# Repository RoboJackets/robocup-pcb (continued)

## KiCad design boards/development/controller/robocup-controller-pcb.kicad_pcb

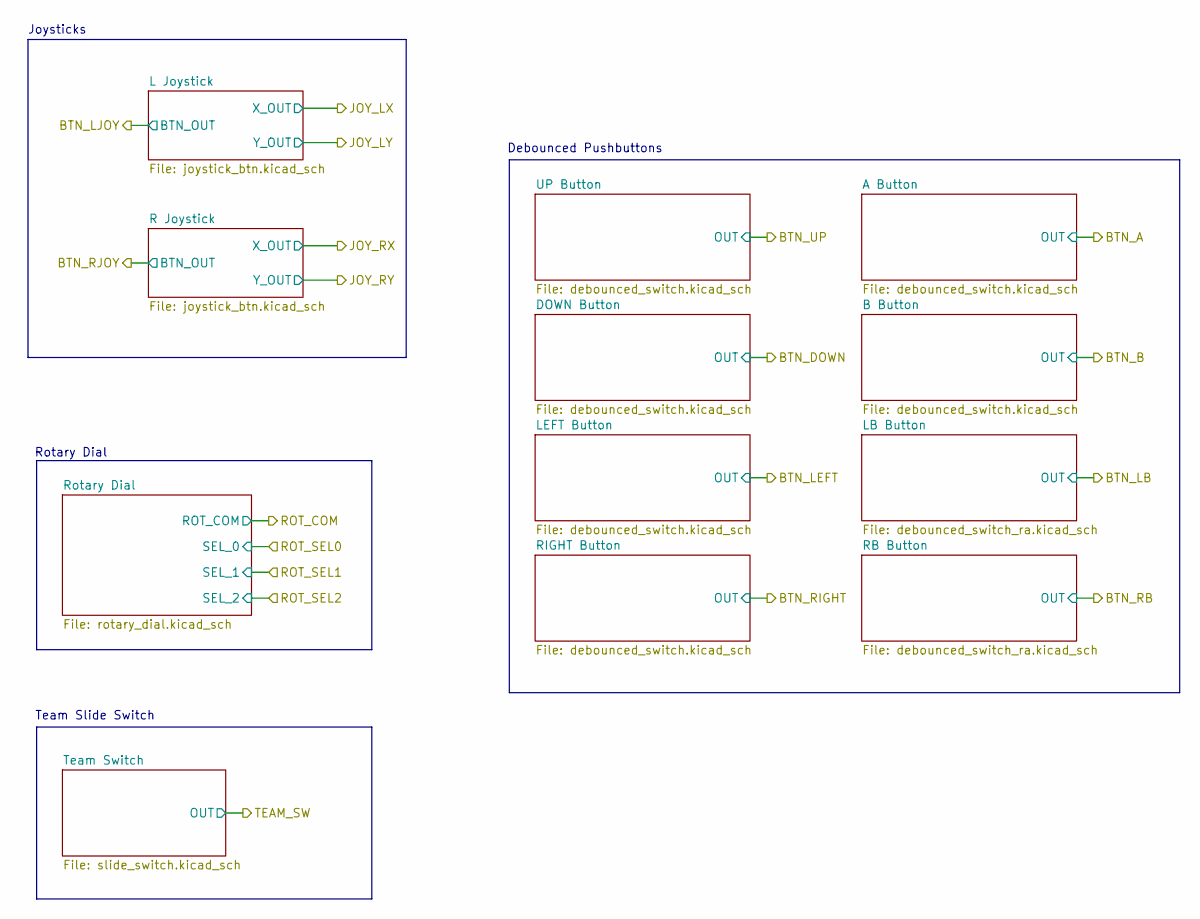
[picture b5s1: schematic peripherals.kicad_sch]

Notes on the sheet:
Debounced Pushbuttons
Joysticks
Team Slide Switch
Rotary Dial

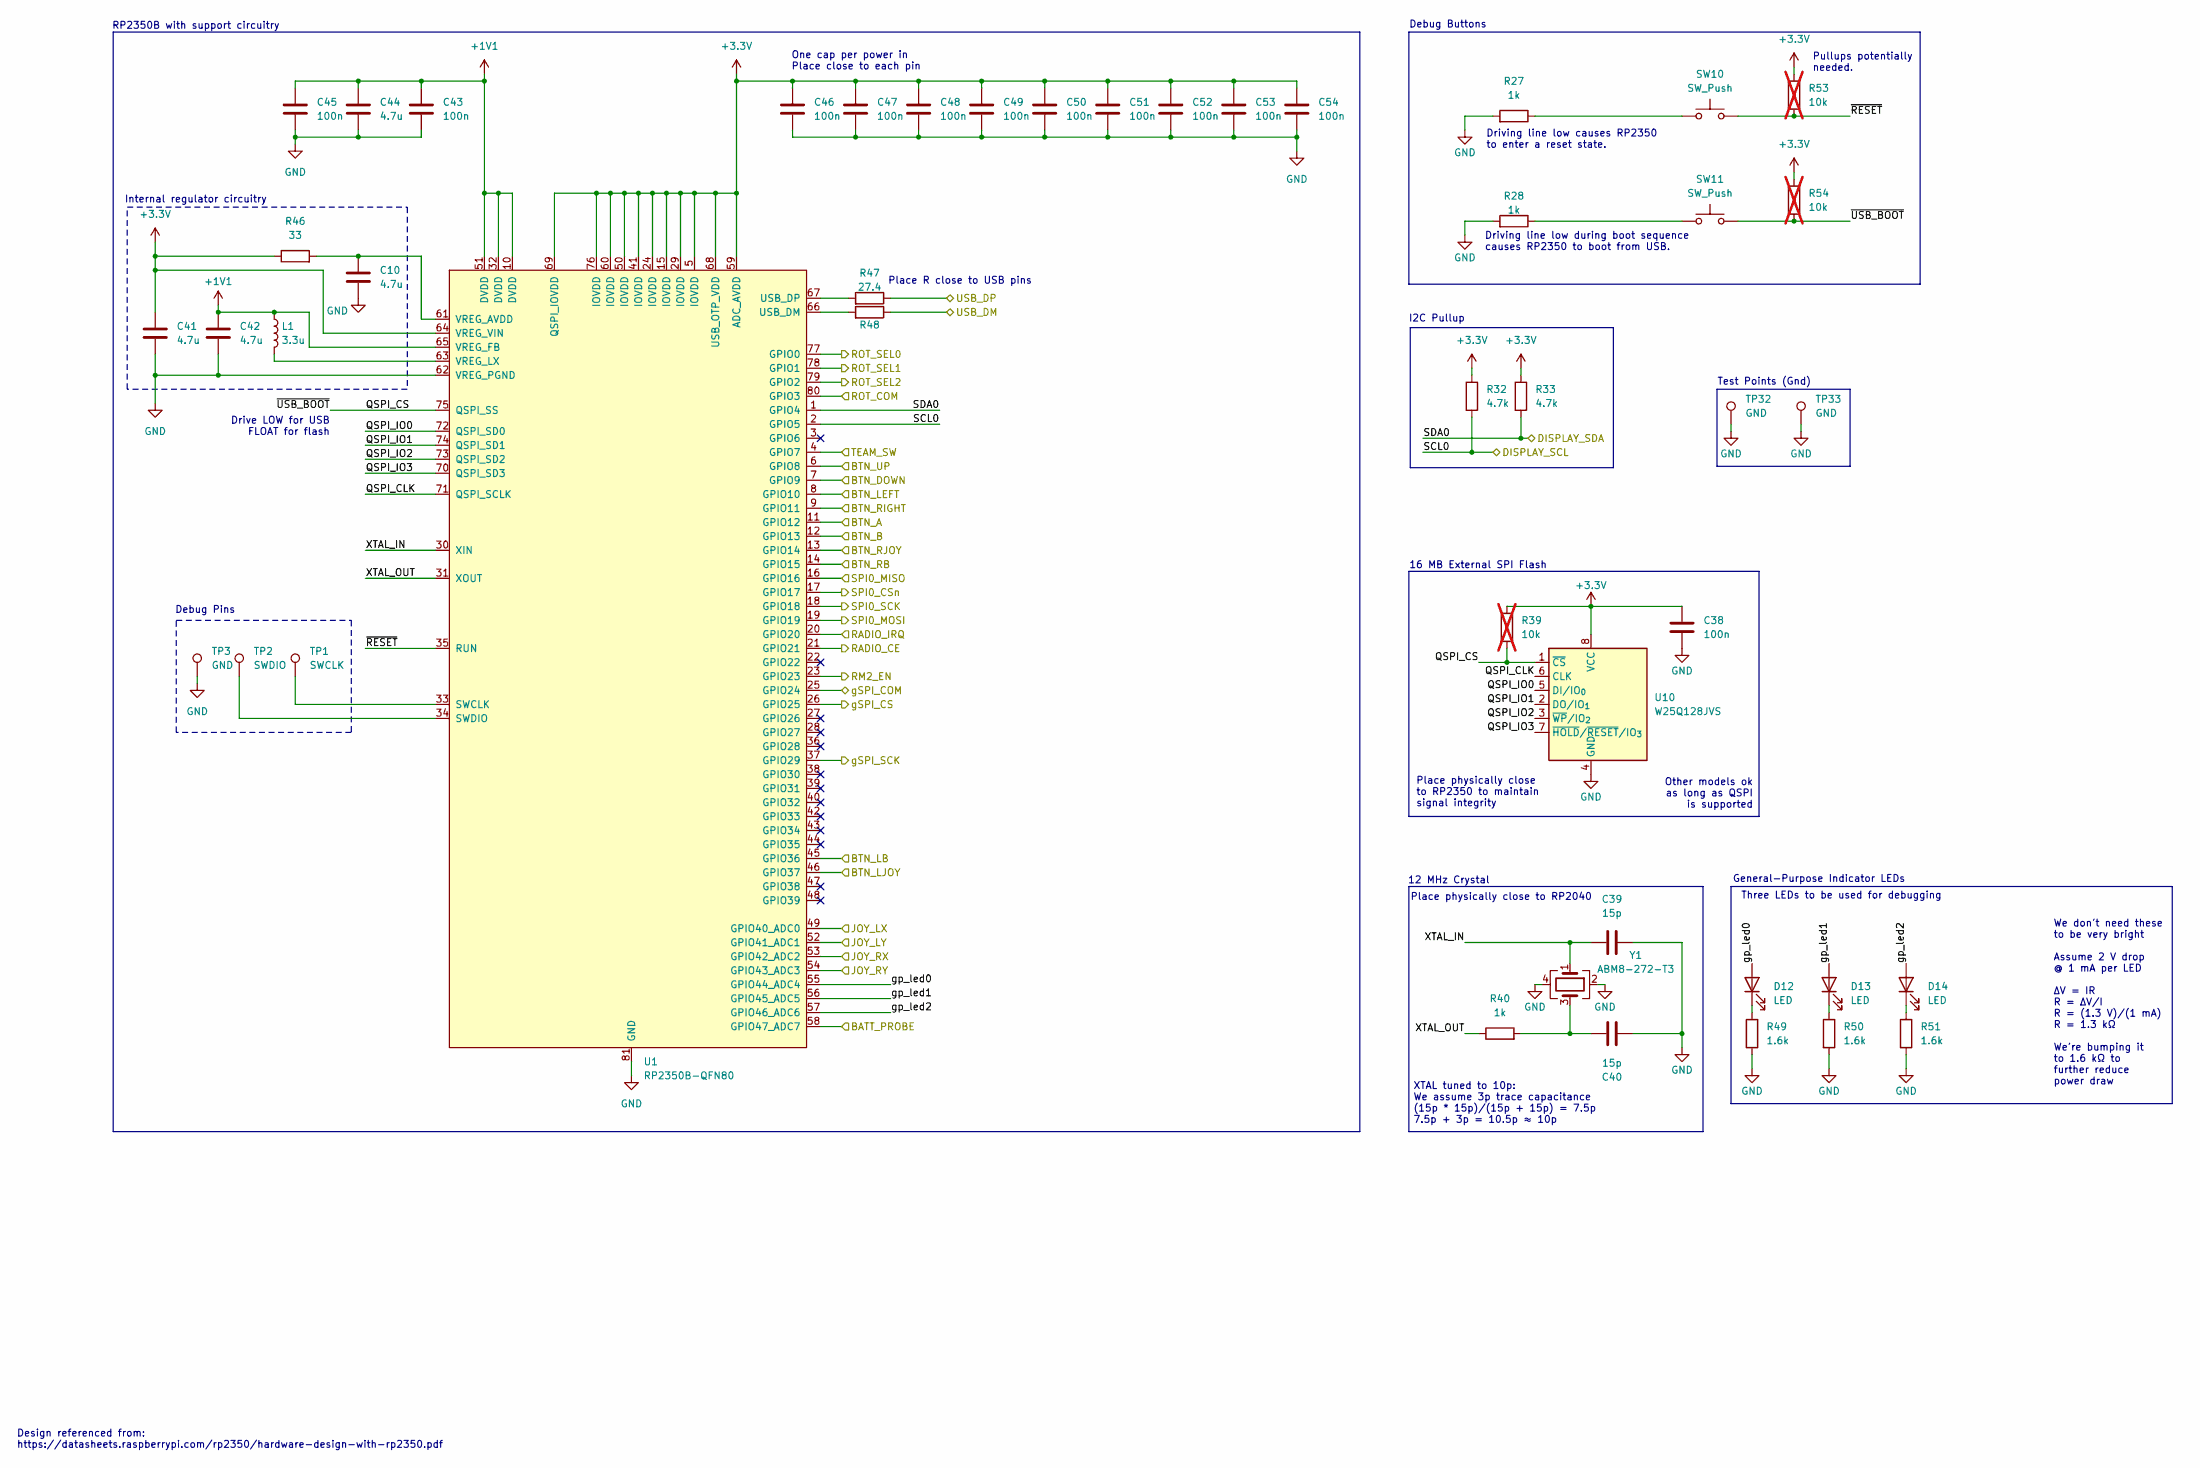
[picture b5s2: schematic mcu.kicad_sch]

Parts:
C10, C41, C42, C44: 4.7u; C_0402_1005Metric
C38, C43, C45, C46, C47, C48, C49, C50, C51, C52, C53, C54: 100n; C_0402_1005Metric
C39, C40: 15p; C_0402_1005Metric
D12, D13, D14: LED; LED_0603_1608Metric
L1: 3.3u; AOTAB201610S3R3101T
R27, R28, R40: 1k; R_0402_1005Metric
R32, R33: 4.7k; R_0402_1005Metric
R39, R53, R54: 10k; R_0402_1005Metric; not fitted
R46: 33; C_0402_1005Metric
R47, R48: 27.4; R_0402_1005Metric
R49, R50, R51: 1.6k; R_0402_1005Metric
SW10, SW11: SW_Push; SW_SKRPABE010
TP1: SWCLK; TestPoint_THTPad_D2.0mm_Drill1.0mm
TP2: SWDIO; TestPoint_THTPad_D2.0mm_Drill1.0mm
TP3: GND; TestPoint_THTPad_2.0x2.0mm_Drill1.0mm
TP32, TP33: GND; TestPoint_Pad_D1.0mm
U1: RP2350B-QFN80; RP2350B_QFN-80_EP_10.573x10.573_Pitch0.4mm
U10: W25Q128JVS; SOIC-8_5.3x5.3mm_P1.27mm; Manufacturer P/N W25Q128JVS
Y1: ABM8-272-T3; Crystal_SMD_Abracon_ABM8AIG-4Pin_3.2x2.5mm; Manufacturer P/N ABM8-272-T3

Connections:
+1V1: C42.1, C43.1, C44.1, C45.1, L1.1, U1.10 (DVDD), U1.32 (DVDD), U1.51 (DVDD), U1.65 (VREG_FB)
+3.3V: C38.1, C41.1, C46.1, C47.1, C48.1, C49.1, C50.1, C51.1, C52.1, C53.1, C54.1, R32.1, R33.1, R39.1, R46.1, R53.1, R54.1, U1.5 (IOVDD), U1.15 (IOVDD), U1.24 (IOVDD), U1.29 (IOVDD), U1.41 (IOVDD), U1.50 (IOVDD), U1.59 (ADC_AVDD), U1.60 (IOVDD), U1.64 (VREG_VIN), U1.68 (USB_OTP_VDD), U1.69 (QSPI_IOVDD), U1.76 (IOVDD), U10.8 (VCC); also elsewhere on the board
/Comms/CE: U1.21 (GPIO21); also elsewhere on the board
/Comms/IRQ: U1.20 (GPIO20); also elsewhere on the board
/Comms/MISO: U1.16 (GPIO16); also elsewhere on the board
/Comms/MOSI: U1.19 (GPIO19); also elsewhere on the board
/Comms/RM2_EN: U1.23 (GPIO23); also elsewhere on the board
/Comms/SCK: U1.18 (GPIO18); also elsewhere on the board
/Comms/gSPI_CS: U1.26 (GPIO25); also elsewhere on the board
/Comms/gSPI_DI: U1.25 (GPIO24); also elsewhere on the board
/Comms/gSPI_SCK: U1.37 (GPIO29); also elsewhere on the board
/Comms/~CS: U1.17 (GPIO17); also elsewhere on the board
/MCU/BATT_PROBE: U1.58 (GPIO47_ADC7); also elsewhere on the board
/MCU/BTN_A: U1.11 (GPIO12); also elsewhere on the board
/MCU/BTN_B: U1.12 (GPIO13); also elsewhere on the board
/MCU/BTN_DOWN: U1.7 (GPIO9); also elsewhere on the board
/MCU/BTN_LB: U1.45 (GPIO36); also elsewhere on the board
/MCU/BTN_LEFT: U1.8 (GPIO10); also elsewhere on the board
/MCU/BTN_LJOY: U1.46 (GPIO37); also elsewhere on the board
/MCU/BTN_RB: U1.14 (GPIO15); also elsewhere on the board
/MCU/BTN_RIGHT: U1.9 (GPIO11); also elsewhere on the board
/MCU/BTN_RJOY: U1.13 (GPIO14); also elsewhere on the board
/MCU/BTN_UP: U1.6 (GPIO8); also elsewhere on the board
/MCU/JOY_LX: U1.49 (GPIO40_ADC0); also elsewhere on the board
/MCU/JOY_LY: U1.52 (GPIO41_ADC1); also elsewhere on the board
/MCU/JOY_RX: U1.53 (GPIO42_ADC2); also elsewhere on the board
/MCU/JOY_RY: U1.54 (GPIO43_ADC3); also elsewhere on the board
/MCU/QSPI_CLK: U1.71 (QSPI_SCLK), U10.6 (CLK)
/MCU/QSPI_CS: R39.2, R54.2, SW11.2, U1.75 (QSPI_SS), U10.1 (~CS)
/MCU/QSPI_IO0: U1.72 (QSPI_SD0), U10.5 (DI/IO_{0})
/MCU/QSPI_IO1: U1.74 (QSPI_SD1), U10.2 (DO/IO_{1})
/MCU/QSPI_IO2: U1.73 (QSPI_SD2), U10.3 (~WP/IO_{2})
/MCU/QSPI_IO3: U1.70 (QSPI_SD3), U10.7 (~HOLD/~RESET/IO_{3})
/MCU/ROT_COM: U1.80 (GPIO3); also elsewhere on the board
/MCU/ROT_SEL0: U1.77 (GPIO0); also elsewhere on the board
/MCU/ROT_SEL1: U1.78 (GPIO1); also elsewhere on the board
/MCU/ROT_SEL2: U1.79 (GPIO2); also elsewhere on the board
/MCU/SCL0: R32.2, U1.2 (GPIO5); also elsewhere on the board
/MCU/SDA0: R33.2, U1.1 (GPIO4); also elsewhere on the board
/MCU/TEAM_SW: U1.4 (GPIO7); also elsewhere on the board
/MCU/USB_DM: R48.1; also elsewhere on the board
/MCU/USB_DP: R47.1; also elsewhere on the board
/MCU/XTAL_IN: C39.2, U1.30 (XIN), Y1.1
/MCU/XTAL_OUT: R40.1, U1.31 (XOUT)
/MCU/gp_led0: D12.2 (A), U1.55 (GPIO44_ADC4)
/MCU/gp_led1: D13.2 (A), U1.56 (GPIO45_ADC5)
/MCU/gp_led2: D14.2 (A), U1.57 (GPIO46_ADC6)
/MCU/~RESET: R53.2, SW10.2, U1.35 (RUN)
GND: C10.2, C38.2, C39.1, C40.2, C41.2, C42.2, C43.2, C44.2, C45.2, C46.2, C47.2, C48.2, C49.2, C50.2, C51.2, C52.2, C53.2, C54.2, R27.2, R28.2, R49.2, R50.2, R51.2, TP3.1 (1_1), TP32.1 (1_1), TP33.1 (1_1), U1.62 (VREG_PGND), U1.81 (GND), U10.4 (GND), Y1.2, Y1.4; also elsewhere on the board
unnamed: C40.1, R40.2, Y1.3
unnamed: D12.1 (K), R49.1
unnamed: D13.1 (K), R50.1
unnamed: D14.1 (K), R51.1
unnamed: R27.1, SW10.1
unnamed: R28.1, SW11.1
unnamed: TP1.1 (1_1), U1.33 (SWCLK)
unnamed: TP2.1 (1_1), U1.34 (SWDIO)
unnamed: R48.2, U1.66 (USB_DM)
unnamed: R47.2, U1.67 (USB_DP)
unnamed: C10.1, R46.2, U1.61 (VREG_AVDD)
unnamed: L1.2, U1.63 (VREG_LX)

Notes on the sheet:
Three LEDs to be used for debugging
XTAL tuned to 10p: We assume 3p trace capacitance (15p * 15p)/(15p + 15p) = 7.5p 7.5p + 3p = 10.5p ≈ 10p
Debug Buttons
Place physically close to RP2350 to maintain signal integrity
Driving line low causes RP2350 to enter a reset state.
Place physically close to RP2040
Design referenced from: https://datasheets.raspberrypi.com/rp2350/hardware-design-with-rp2350.pdf
RP2350B with support circuitry
We don't need these to be very bright Assume 2 V drop @ 1 mA per LED ΔV = IR R = ΔV/I R = (1.3 V)/(1 mA) R = 1.3 kΩ We're bumping it to 1.6 kΩ to further reduce power draw
General-Purpose Indicator LEDs
Pullups potentially needed.
12 MHz Crystal
Driving line low during boot sequence causes RP2350 to boot from USB.
Internal regulator circuitry
Place R close to USB pins
One cap per power in Place close to each pin
16 MB External SPI Flash
Other models ok as long as QSPI is supported
Drive LOW for USB FLOAT for flash
Debug Pins
Test Points (Gnd)
I2C Pullup

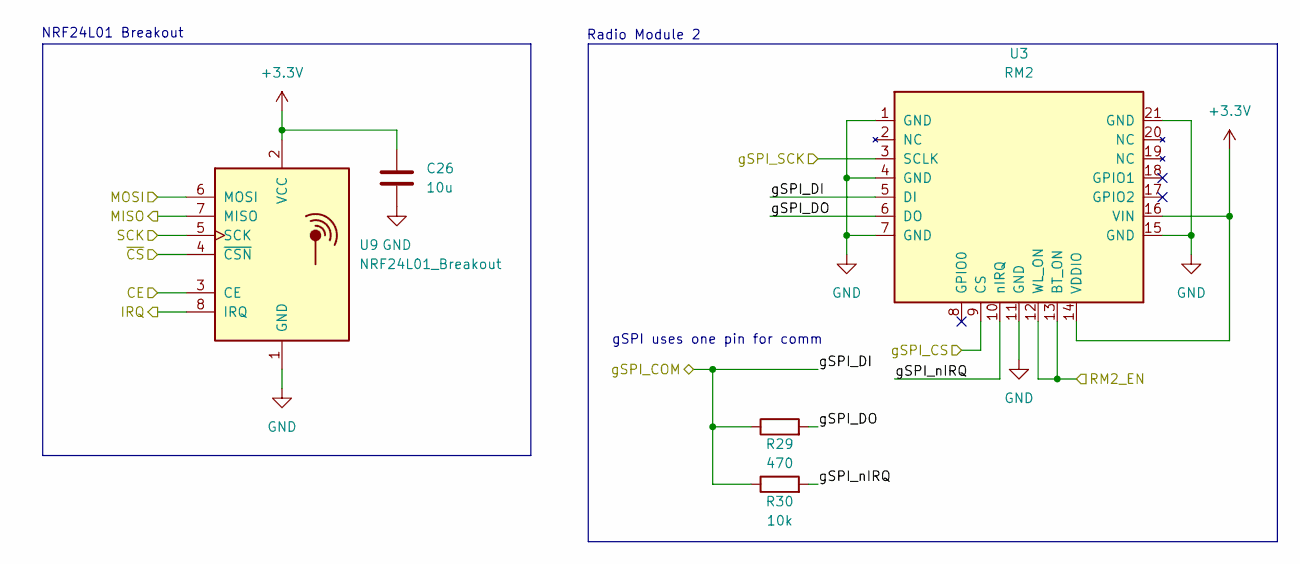
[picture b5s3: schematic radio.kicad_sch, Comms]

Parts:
C26: 10u; C_0603_1608Metric
R29: 470; R_0402_1005Metric
R30: 10k; R_0402_1005Metric
U3: RM2; rpi_rmc20452t
U9: NRF24L01_Breakout; nRF24L01_Breakout

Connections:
+3.3V: C26.2, U3.14 (VDDIO), U3.16 (VIN), U9.2 (VCC); also elsewhere on the board
/Comms/CE: U9.3 (CE); also elsewhere on the board
/Comms/IRQ: U9.8 (IRQ); also elsewhere on the board
/Comms/MISO: U9.7 (MISO); also elsewhere on the board
/Comms/MOSI: U9.6 (MOSI); also elsewhere on the board
/Comms/RM2_EN: U3.12 (WL_ON), U3.13 (BT_ON); also elsewhere on the board
/Comms/SCK: U9.5 (SCK); also elsewhere on the board
/Comms/gSPI_CS: U3.9 (CS); also elsewhere on the board
/Comms/gSPI_DI: R29.1, R30.1, U3.5 (DI); also elsewhere on the board
/Comms/gSPI_DO: R29.2, U3.6 (DO)
/Comms/gSPI_SCK: U3.3 (SCLK); also elsewhere on the board
/Comms/gSPI_nIRQ: R30.2, U3.10 (nIRQ)
/Comms/~CS: U9.4 (~CSN); also elsewhere on the board
GND: C26.1, U3.1 (GND), U3.4 (GND), U3.7 (GND), U3.11 (GND), U3.15 (GND), U3.21 (GND), U9.1 (GND); also elsewhere on the board

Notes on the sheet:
NRF24L01 Breakout
gSPI uses one pin for comm
Radio Module 2

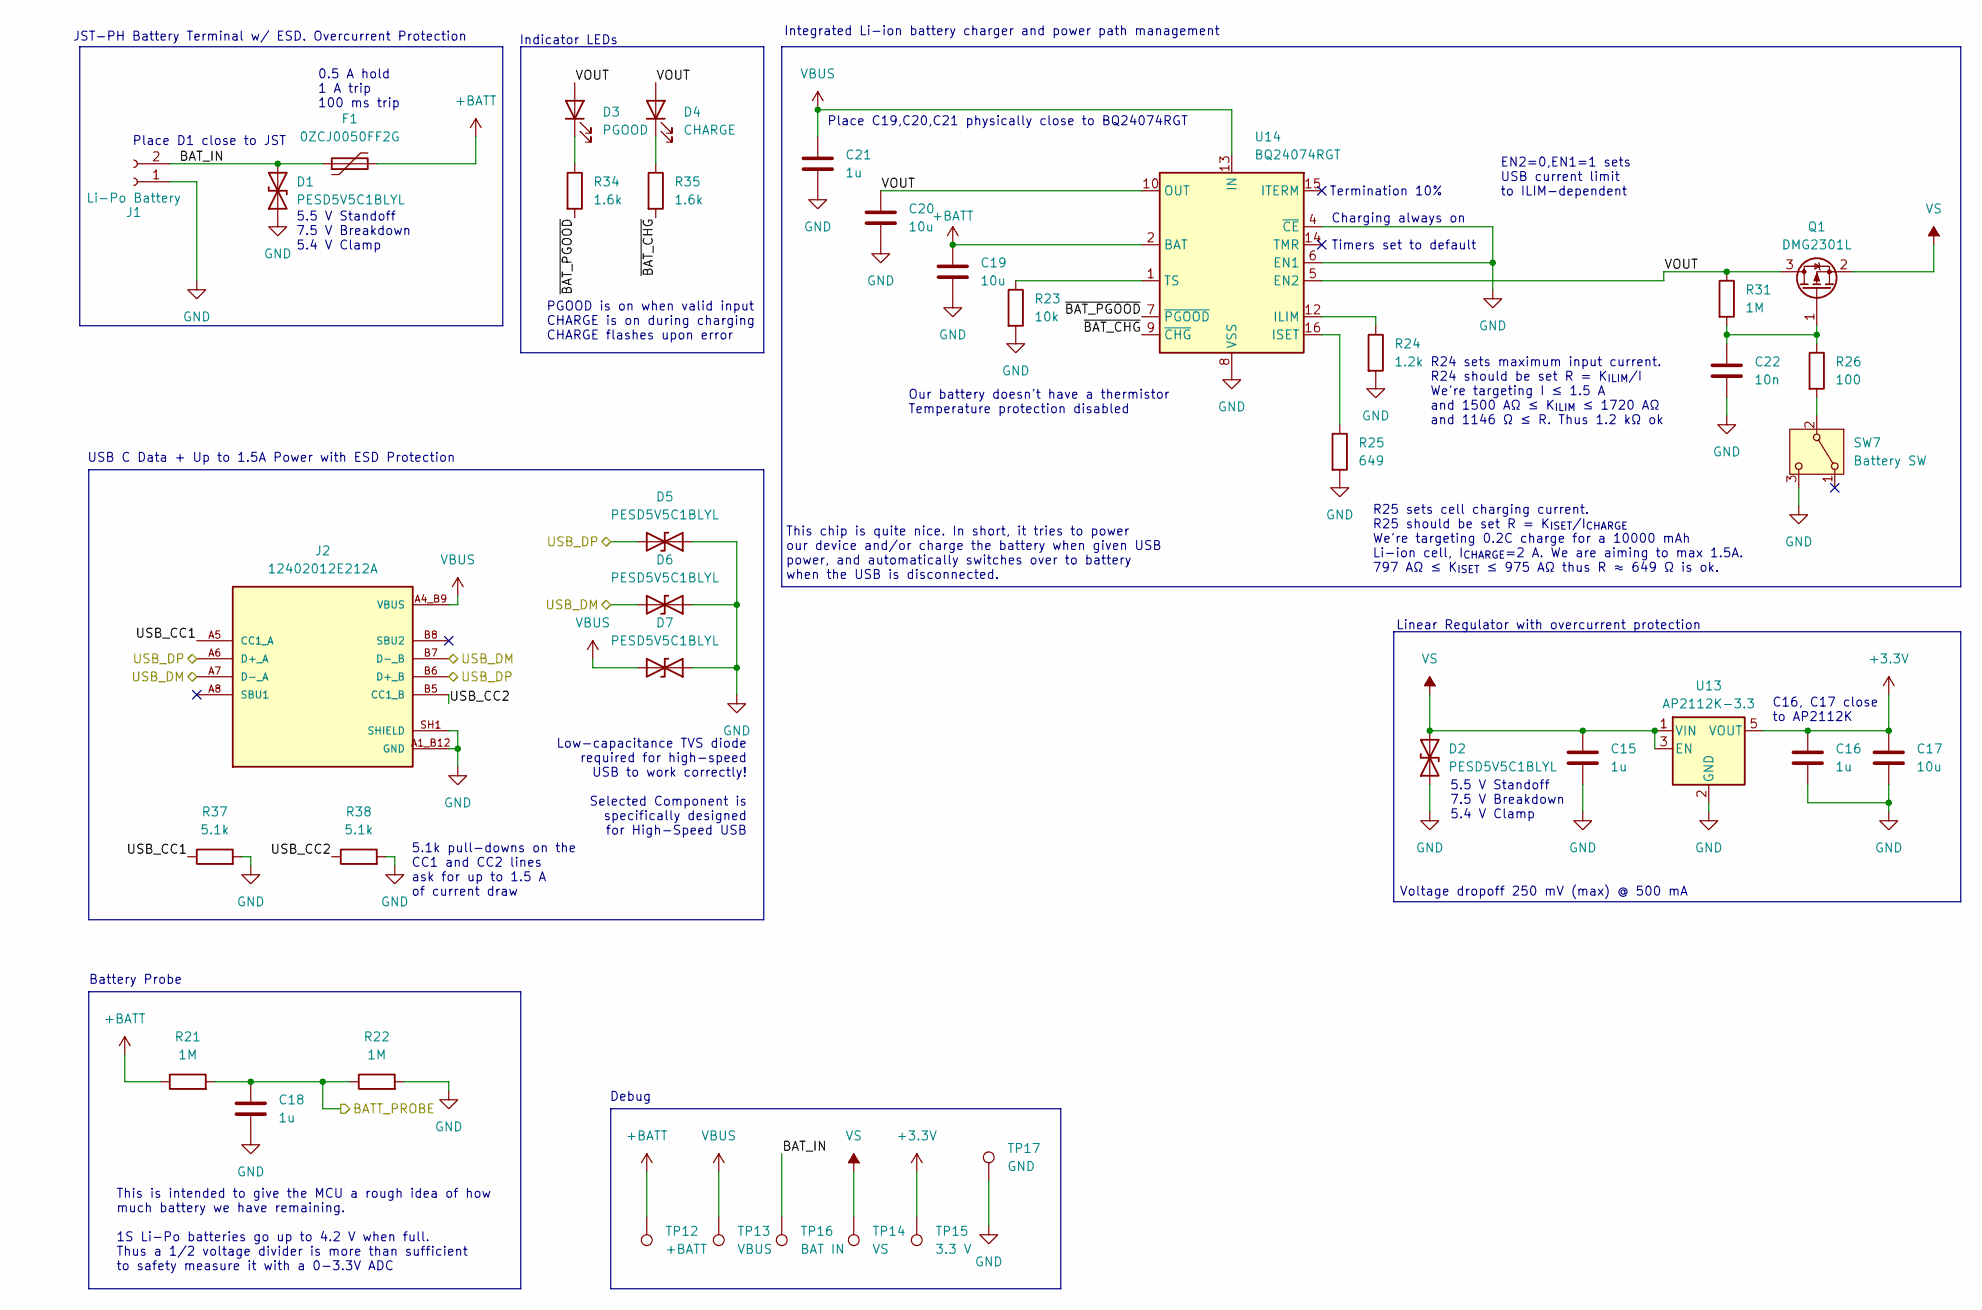
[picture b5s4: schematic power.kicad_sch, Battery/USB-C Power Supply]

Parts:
C15, C16, C18, C21: 1u; C_0402_1005Metric
C17, C19, C20: 10u; C_0402_1005Metric
C22: 10n; C_0402_1005Metric
D1, D2, D5, D6, D7: PESD5V5C1BLYL; D_SOD-882D
D3: PGOOD; LED_0603_1608Metric
D4: CHARGE; LED_0603_1608Metric
F1: 0ZCJ0050FF2G; Fuse_1206_3216Metric
J1: Li-Po Battery; JST_PH_S2B-PH-K_1x02_P2.00mm_Horizontal
J2: 12402012E212A; AMPHENOL_12402012E212A; PARTREV 4
Q1: DMG2301L; SOT-23
R21, R22, R31: 1M; R_0402_1005Metric
R23: 10k; R_0402_1005Metric
R24: 1.2k; R_0402_1005Metric
R25: 649; R_0402_1005Metric
R26: 100; R_0402_1005Metric
R34, R35: 1.6k; R_0402_1005Metric
R37, R38: 5.1k; R_0402_1005Metric
SW7: Battery SW; OS102011MA1QN1_CNK
TP12: +BATT; TestPoint_Pad_D1.0mm
TP13: VBUS; TestPoint_Pad_D1.0mm
TP14: VS; TestPoint_Pad_D1.0mm
TP15: 3.3 V; TestPoint_Pad_D1.0mm
TP16: BAT IN; TestPoint_Pad_D1.0mm
TP17: GND; TestPoint_Pad_D1.0mm
U13: AP2112K-3.3; SOT-23-5
U14: BQ24074RGT; VQFN-16-1EP_3x3mm_P0.5mm_EP1.6x1.6mm

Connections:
+3.3V: C16.1, C17.1, TP15.1 (1_1), U13.5 (VOUT); also elsewhere on the board
+BATT: C19.1, F1.2, R21.1, TP12.1 (1_1), U14.2 (BAT), U14.3 (BAT)
/MCU/BATT_PROBE: C18.1, R21.2, R22.1; also elsewhere on the board
/MCU/USB_DM: D6.2 (A2), J2.A7 (D-_A), J2.B7 (D-_B); also elsewhere on the board
/MCU/USB_DP: D5.2 (A2), J2.A6 (D+_A), J2.B6 (D+_B); also elsewhere on the board
/Power/BAT_IN: D1.2 (A2), F1.1, J1.2, TP16.1 (1_1)
/Power/USB_CC1: J2.A5 (CC1_A), R37.1
/Power/USB_CC2: J2.B5 (CC1_B), R38.1
/Power/VOUT: C20.1, D3.2 (A), D4.2 (A), Q1.3 (D), R31.1, U14.5 (EN2), U14.10 (OUT), U14.11 (OUT)
/Power/~BAT_CHG: R35.2, U14.9 (~CHG)
/Power/~BAT_PGOOD: R34.2, U14.7 (~PGOOD)
GND: C15.2, C16.2, C17.2, C18.2, C19.2, C20.2, C21.2, C22.2, D1.1 (A1), D2.1 (A1), D5.1 (A1), D6.1 (A1), D7.1 (A1), J1.1, J2.A1_B12 (GND), J2.B1_A12 (GND), J2.SH1 (SHIELD), J2.SH2 (SHIELD), J2.SH3 (SHIELD), J2.SH4 (SHIELD), R22.2, R23.2, R24.2, R25.2, R37.2, R38.2, SW7.3 (C), TP17.1 (1_1), U13.2 (GND), U14.4 (~CE), U14.6 (EN1), U14.8 (VSS), U14.17 (VSS); also elsewhere on the board
unnamed: D3.1 (K), R34.1
unnamed: D4.1 (K), R35.1
unnamed: C22.1, Q1.1 (G), R26.1, R31.2
unnamed: R26.2, SW7.2 (B)
unnamed: R24.1, U14.12 (ILIM)
unnamed: R25.1, U14.16 (ISET)
unnamed: R23.1, U14.1 (TS)
VBUS: C21.1, D7.2 (A2), J2.A4_B9 (VBUS), J2.B4_A9 (VBUS), TP13.1 (1_1), U14.13 (IN)
VS: C15.1, D2.2 (A2), Q1.2 (S), TP14.1 (1_1), U13.1 (VIN), U13.3 (EN)

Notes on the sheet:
Termination 10%
R25 sets cell charging current. R25 should be set R = K_{ISET}/I_{CHARGE} We're targeting 0.2C charge for a 10000 mAh Li-ion cell, I_{CHARGE}=2 A. We are aiming to max 1.5A. 797 AΩ ≤ K_{ISET} ≤ 975 AΩ thus R ≈ 649 Ω is ok.
Indicator LEDs
This chip is quite nice. In short, it tries to power our device and/or charge the battery when given USB power, and automatically switches over to battery when the USB is disconnected.
R24 sets maximum input current. R24 should be set R = K_{ILIM}/I We're targeting I ≤ 1.5 A and 1500 AΩ ≤ K_{ILIM} ≤ 1720 AΩ and 1146 Ω ≤ R. Thus 1.2 kΩ ok
Battery Probe
EN2=0,EN1=1 sets USB current limit to ILIM-dependent
0.5 A hold 1 A trip 100 ms trip
This is intended to give the MCU a rough idea of how much battery we have remaining. 1S Li-Po batteries go up to 4.2 V when full. Thus a 1/2 voltage divider is more than sufficient to safety measure it with a 0-3.3V ADC
Debug
5.1k pull-downs on the CC1 and CC2 lines ask for up to 1.5 A of current draw
Place D1 close to JST
5.5 V Standoff 7.5 V Breakdown 5.4 V Clamp
Charging always on
Voltage dropoff 250 mV (max) @ 500 mA
Integrated Li-ion battery charger and power path management
Timers set to default
Our battery doesn't have a thermistor Temperature protection disabled
C16, C17 close to AP2112K
PGOOD is on when valid input CHARGE is on during charging CHARGE flashes upon error
Low-capacitance TVS diode required for high-speed USB to work correctly! Selected Component is specifically designed for High-Speed USB
Place C19,C20,C21 physically close to BQ24074RGT
USB C Data + Up to 1.5A Power with ESD Protection
JST-PH Battery Terminal w/ ESD. Overcurrent Protection
Linear Regulator with overcurrent protection

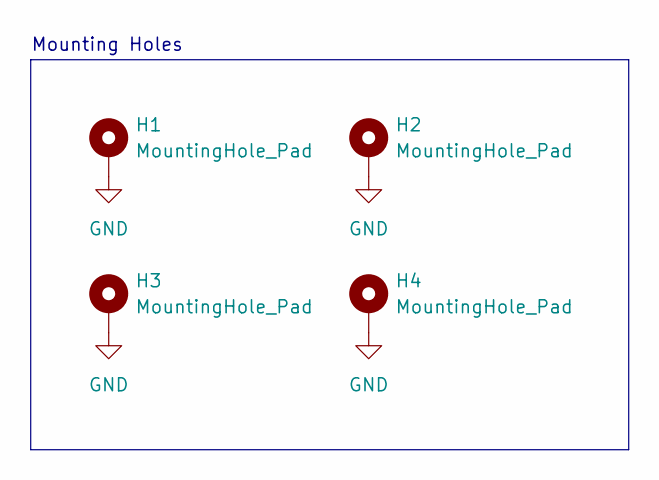
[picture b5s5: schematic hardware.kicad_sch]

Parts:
H1, H2, H3, H4: MountingHole_Pad; MountingHole_4mm_Pad_TopBottom

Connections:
GND: H1.1 (1_1), H2.1 (1_1), H3.1 (1_1), H4.1 (1_1); also elsewhere on the board

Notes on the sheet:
Mounting Holes

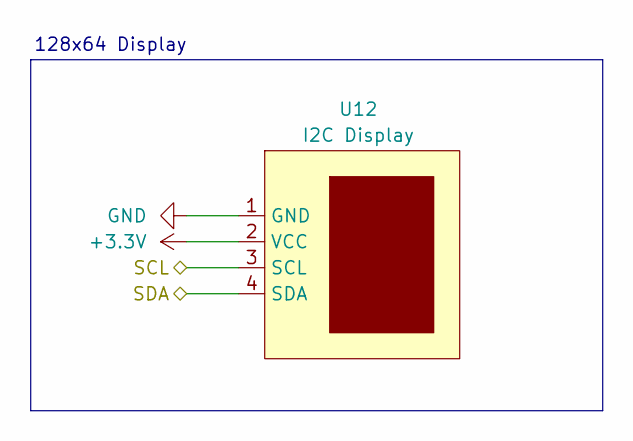
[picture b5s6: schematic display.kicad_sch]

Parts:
U12: I2C Display; LCD_OLED_128X64_1.3_I2C

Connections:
+3.3V: U12.2 (VCC); also elsewhere on the board
/MCU/SCL0: U12.3 (SCL); also elsewhere on the board
/MCU/SDA0: U12.4 (SDA); also elsewhere on the board
GND: U12.1 (GND); also elsewhere on the board

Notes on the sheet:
128x64 Display

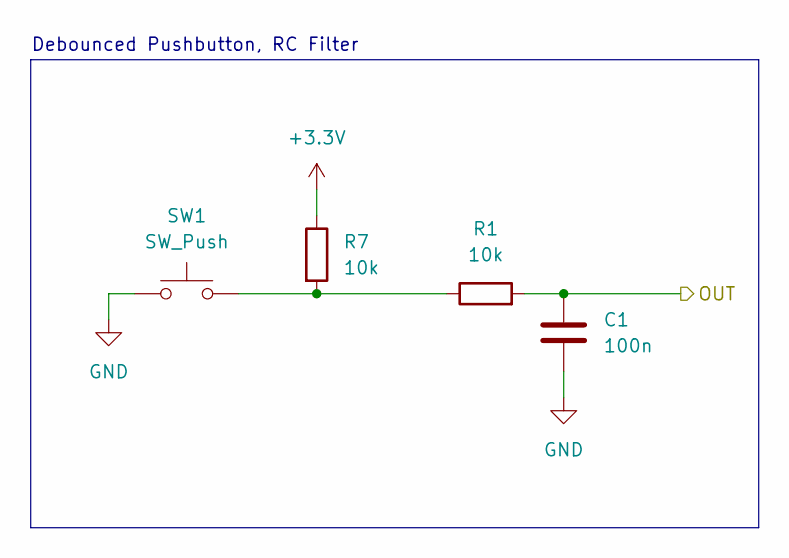
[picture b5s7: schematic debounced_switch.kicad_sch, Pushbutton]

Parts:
C1: 100n; C_0402_1005Metric
R1, R7: 10k; R_0402_1005Metric
SW1: SW_Push; SW_PUSH-12mm

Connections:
+3.3V: R7.1; also elsewhere on the board
/MCU/BTN_A: C1.1, R1.2; also elsewhere on the board
GND: C1.2, SW1.1; also elsewhere on the board
unnamed: R1.1, R7.2, SW1.2

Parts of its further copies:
C2, C3, C4, C5, C6: 100n; C_0402_1005Metric
R2, R3, R4, R5, R6, R8, R9, R10, R11, R12: 10k; R_0402_1005Metric
SW2, SW3, SW4, SW5, SW6: SW_Push; SW_PUSH-12mm

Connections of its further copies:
+3.3V: R8.1, R9.1, R10.1, R11.1, R12.1; also elsewhere on the board
/MCU/BTN_B: C2.1, R2.2; also elsewhere on the board
/MCU/BTN_DOWN: C4.1, R4.2; also elsewhere on the board
/MCU/BTN_LEFT: C5.1, R5.2; also elsewhere on the board
/MCU/BTN_RIGHT: C6.1, R6.2; also elsewhere on the board
/MCU/BTN_UP: C3.1, R3.2; also elsewhere on the board
GND: C2.2, C3.2, C4.2, C5.2, C6.2, SW2.1, SW3.1, SW4.1, SW5.1, SW6.1; also elsewhere on the board
unnamed: R2.1, R8.2, SW2.2
unnamed: R3.1, R9.2, SW3.2
unnamed: R4.1, R10.2, SW4.2
unnamed: R5.1, R11.2, SW5.2
unnamed: R6.1, R12.2, SW6.2

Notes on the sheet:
Debounced Pushbutton, RC Filter

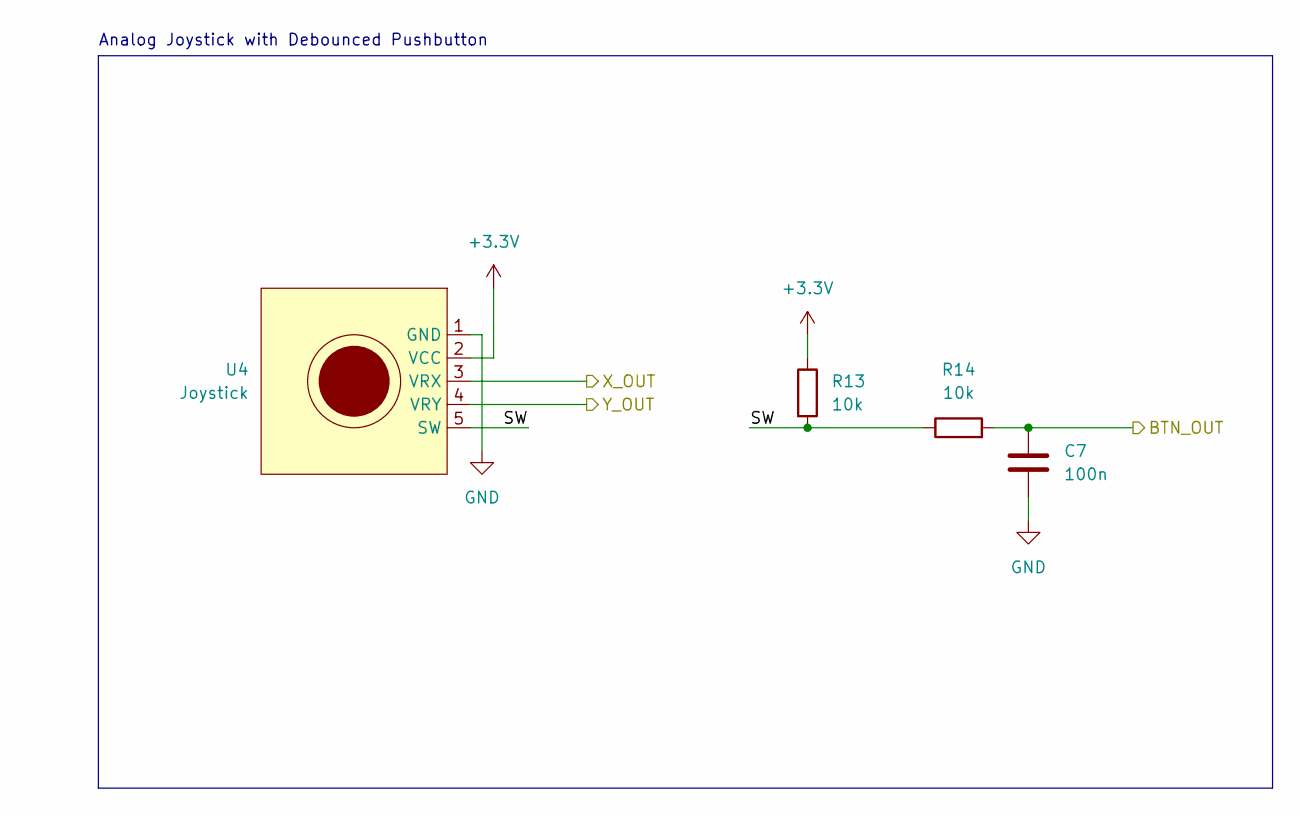
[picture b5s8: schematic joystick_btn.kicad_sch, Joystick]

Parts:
C7: 100n; C_0402_1005Metric
R13, R14: 10k; R_0402_1005Metric
U4: Joystick; Joystick_Breakout

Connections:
+3.3V: R13.1, U4.2 (VCC); also elsewhere on the board
/MCU/BTN_LJOY: C7.1, R14.2; also elsewhere on the board
/MCU/JOY_LX: U4.3 (VRX); also elsewhere on the board
/MCU/JOY_LY: U4.4 (VRY); also elsewhere on the board
/Peripherals/L Joystick/SW: R13.2, R14.1, U4.5 (SW)
GND: C7.2, U4.1 (GND); also elsewhere on the board

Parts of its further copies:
C8: 100n; C_0402_1005Metric
R15, R16: 10k; R_0402_1005Metric
U5: Joystick; Joystick_Breakout

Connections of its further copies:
+3.3V: R15.1, U5.2 (VCC); also elsewhere on the board
/MCU/BTN_RJOY: C8.1, R16.2; also elsewhere on the board
/MCU/JOY_RX: U5.3 (VRX); also elsewhere on the board
/MCU/JOY_RY: U5.4 (VRY); also elsewhere on the board
/Peripherals/R Joystick/SW: R15.2, R16.1, U5.5 (SW)
GND: C8.2, U5.1 (GND); also elsewhere on the board

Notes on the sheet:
Analog Joystick with Debounced Pushbutton

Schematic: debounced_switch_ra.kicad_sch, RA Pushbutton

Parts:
C24: 100n; C_0402_1005Metric
R41, R42: 10k; R_0402_1005Metric
S1: TS11-674-43-BK-160-RA-D; SW_TS11-674-43-BK-160-RA-D; PARTREV 1.01

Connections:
+3.3V: R41.1; also elsewhere on the board
/MCU/BTN_LB: C24.1, R42.2; also elsewhere on the board
GND: C24.2, S1.2, S1.3 (GND), S1.4 (GND); also elsewhere on the board
unnamed: R41.2, R42.1, S1.1

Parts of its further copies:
C25: 100n; C_0402_1005Metric
R43, R44: 10k; R_0402_1005Metric
S2: TS11-674-43-BK-160-RA-D; SW_TS11-674-43-BK-160-RA-D; PARTREV 1.01

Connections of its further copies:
+3.3V: R43.1; also elsewhere on the board
/MCU/BTN_RB: C25.1, R44.2; also elsewhere on the board
GND: C25.2, S2.2, S2.3 (GND), S2.4 (GND); also elsewhere on the board
unnamed: R43.2, R44.1, S2.1

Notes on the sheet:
Debounced Right Angled Pushbutton, RC Filter

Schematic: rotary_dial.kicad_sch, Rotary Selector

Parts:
C23: 100n; C_0402_1005Metric
R17, R18, R19, R20, R36, R45: 10k; R_0402_1005Metric
U2: SS-10-16NP-LE
U15: 74HCT4051; SOIC-16_3.9x9.9mm_P1.27mm

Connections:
+3.3V: C23.1, U2.2 (C), U2.7 (C), U15.16 (VCC); also elsewhere on the board
/MCU/ROT_COM: U15.3 (A); also elsewhere on the board
/MCU/ROT_SEL0: U15.11 (S0); also elsewhere on the board
/MCU/ROT_SEL1: U15.10 (S1); also elsewhere on the board
/MCU/ROT_SEL2: U15.9 (S2); also elsewhere on the board
/Peripherals/Rotary Dial/PIN1: R45.1, U2.1, U15.13 (A0)
/Peripherals/Rotary Dial/PIN2: R36.1, U2.3 (2), U15.14 (A1)
/Peripherals/Rotary Dial/PIN3: R17.1, U2.4 (3), U15.15 (A2)
/Peripherals/Rotary Dial/PIN4: R20.1, U2.5 (4), U15.12 (A3)
/Peripherals/Rotary Dial/PIN5: R19.1, U2.6 (5), U15.1 (A4)
/Peripherals/Rotary Dial/PIN6: R18.1, U2.8 (6), U15.5 (A5)
GND: C23.2, R17.2, R18.2, R19.2, R20.2, R36.2, R45.2, U15.2 (A6), U15.4 (A7), U15.6 (~E), U15.7 (VEE), U15.8 (GND); also elsewhere on the board

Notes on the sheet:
Switching voltages = (V_CC - V_EE) so V_EE = 0V
6:1 Rotary Switch
8:1 Mux
A6,A7 are possible inputs depending on implementation so tie to gnd for safety

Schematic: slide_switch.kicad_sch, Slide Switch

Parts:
R52: 10k; R_0402_1005Metric
S4: OS102011MS2QN1; OS102011MA1QN1; Mouser Part Number 611-OS102011MS2QN1

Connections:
+3.3V: R52.1; also elsewhere on the board
/MCU/TEAM_SW: S4.2; also elsewhere on the board
GND: S4.3, S4.4 (GND), S4.5 (GND); also elsewhere on the board
unnamed: R52.2, S4.1

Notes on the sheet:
Team Slide Switch

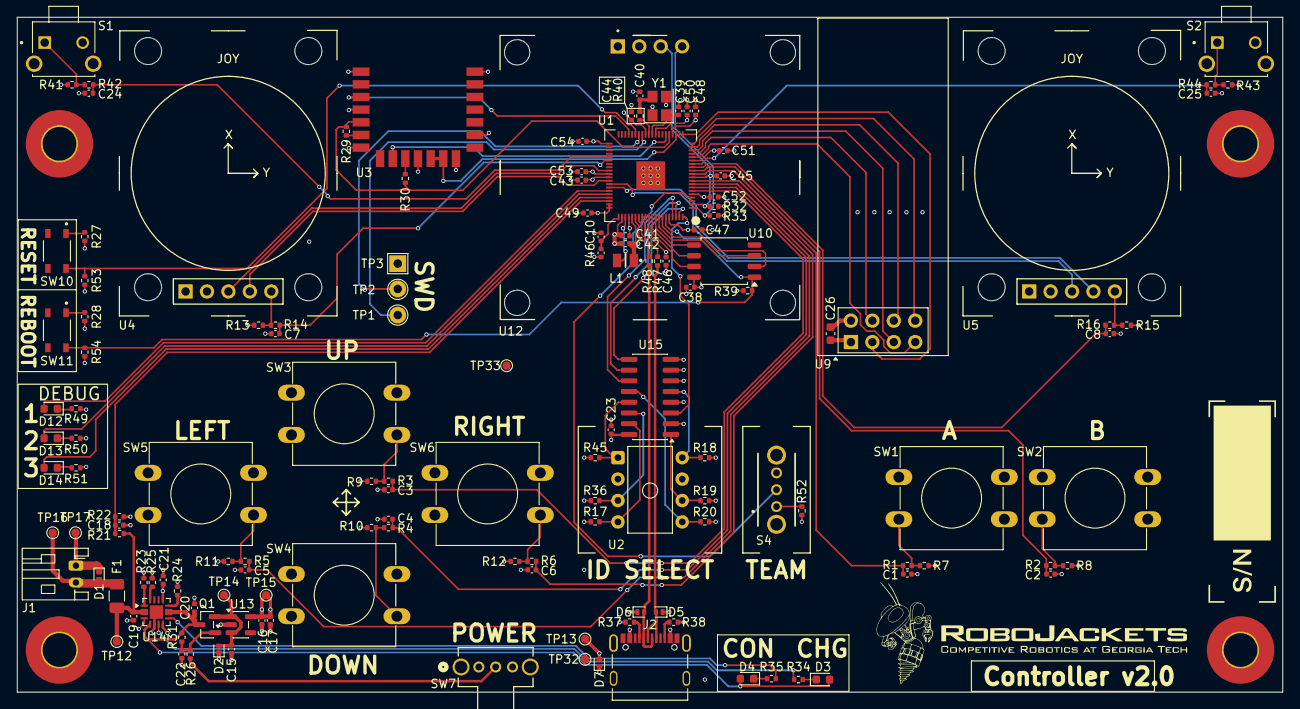
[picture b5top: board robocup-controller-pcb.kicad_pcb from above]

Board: 4 copper layers, 150.0 x 80.0 mm, 146 parts (0 on the bottom side), 96 nets.
